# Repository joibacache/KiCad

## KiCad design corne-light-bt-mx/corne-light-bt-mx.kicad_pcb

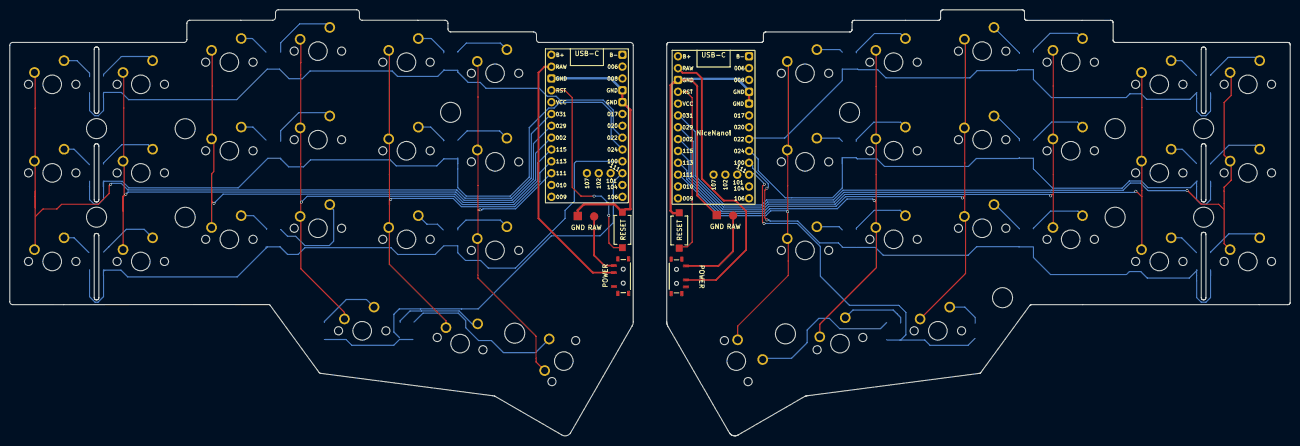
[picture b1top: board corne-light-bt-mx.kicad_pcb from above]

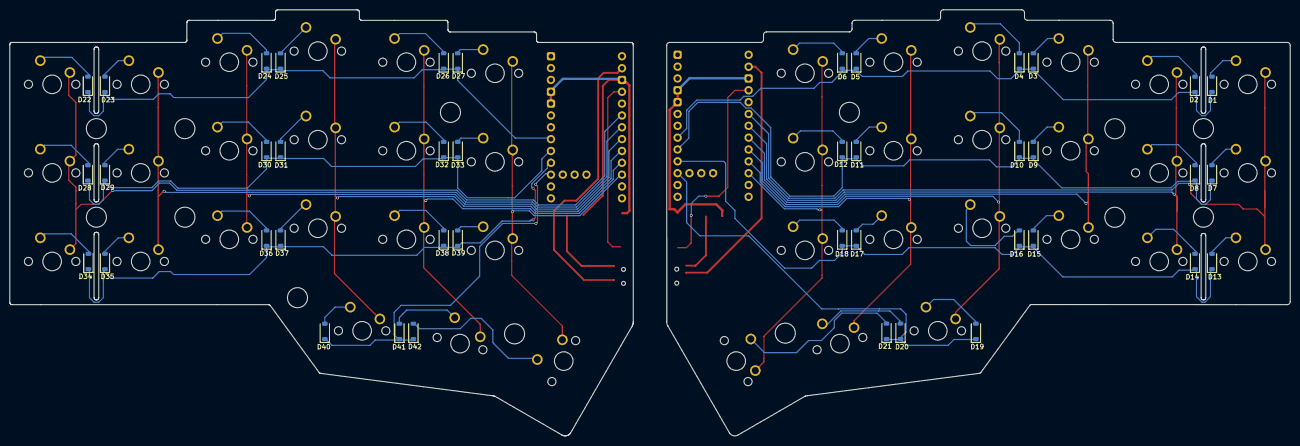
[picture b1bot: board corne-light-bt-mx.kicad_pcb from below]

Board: 2 copper layers, 274.7 x 91.4 mm, 101 parts (44 on the bottom side), 62 nets.

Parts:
D1, D2, D3, D4, D5, D6, D7, D8, D9, D10, D11, D12, D13, D14, D15, D16, D17, D18, D19, D20, D21, D22, D23, D24, D25, D26, D27, D28, D29, D30, D31, D32, D33, D34, D35, D36, D37, D38, D39, D40, D41, D42: D; D_SOD-123
RSW1, RSW2: SW_PUSH; SMD 2Pin Switch
Ref**: Val**; spacer_m2
Ref**#2, Ref**#3, Ref**#4, Ref**#5, Ref**#6, Ref**#7, Ref**#8, Ref**#9, Ref**#10, Ref**#11, Ref**#12, Ref**#13: Val**; spacer_m2
SW1, SW2, SW3, SW4, SW5, SW6, SW7, SW8, SW9, SW10, SW11, SW12, SW13, SW14, SW15, SW16, SW17, SW18, SW19, SW20, SW22, SW23, SW24, SW25, SW26, SW27, SW28, SW29, SW30, SW31, SW32, SW33, SW34, SW35, SW36, SW37, SW38, SW39, SW40, SW41: SW_PUSH; SW_MX_1u
SW21, SW42: SW_PUSH; SW_MX_1.5u
U1, U2: NiceNano!; nice_nano_v2_full

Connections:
unnamed: D1.2, SW1.2
unnamed: D2.2, SW2.2
unnamed: D3.2, SW3.2
unnamed: D4.2, SW4.2
unnamed: D5.2, SW5.2
unnamed: D6.2, SW6.2
unnamed: D7.2, SW7.2
unnamed: D8.2, SW8.2
unnamed: D9.2, SW9.2
unnamed: D10.2, SW10.2
unnamed: D11.2, SW11.2
unnamed: D12.2, SW12.2
unnamed: D13.2, SW13.2
unnamed: D14.2, SW14.2
unnamed: D15.2, SW15.2
unnamed: D16.2, SW16.2
unnamed: D17.2, SW17.2
unnamed: D18.2, SW18.2
unnamed: D19.2, SW19.2
unnamed: D20.2, SW20.2
unnamed: D21.2, SW21.2
unnamed: D22.2, SW22.2
unnamed: D23.2, SW23.2
unnamed: D24.2, SW24.2
unnamed: D25.2, SW25.2
unnamed: D26.2, SW26.2
unnamed: D27.2, SW27.2
unnamed: D28.2, SW28.2
unnamed: D29.2, SW29.2
unnamed: D30.2, SW30.2
unnamed: D31.2, SW31.2
unnamed: D32.2, SW32.2
unnamed: D33.2, SW33.2
unnamed: D34.2, SW34.2
unnamed: D35.2, SW35.2
unnamed: D36.2, SW36.2
unnamed: D37.2, SW37.2
unnamed: D38.2, SW38.2
unnamed: D39.2, SW39.2
unnamed: D40.2, SW40.2
unnamed: D41.2, SW41.2
unnamed: D42.2, SW42.2
col0: SW1.1, SW7.1, SW13.1
col0_r: SW22.1, SW28.1, SW34.1
col1: SW2.1, SW8.1, SW14.1
col1_r: SW23.1, SW29.1, SW35.1
col2: SW3.1, SW9.1, SW15.1
col2_r: SW24.1, SW30.1, SW36.1
col3: SW4.1, SW10.1, SW16.1, SW19.1
col3_r: SW25.1, SW31.1, SW37.1, SW40.1
col4: SW5.1, SW11.1, SW17.1, SW20.1
col4_r: SW26.1, SW32.1, SW38.1, SW41.1
col5: SW6.1, SW12.1, SW18.1, SW21.1
col5_r: SW27.1, SW33.1, SW39.1, SW42.1
row0: D1.1, D2.1, D3.1, D4.1, D5.1, D6.1
row0_r: D22.1, D23.1, D24.1, D25.1, D26.1, D27.1
row1: D7.1, D8.1, D9.1, D10.1, D11.1, D12.1
row1_r: D28.1, D29.1, D30.1, D31.1, D32.1, D33.1
row2: D13.1, D14.1, D15.1, D16.1, D17.1, D18.1
row2_r: D34.1, D35.1, D36.1, D37.1, D38.1, D39.1
row3: D19.1, D20.1, D21.1
row3_r: D40.1, D41.1, D42.1

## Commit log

2024-04-25 First checkin
2024-04-25 Added .gitignore based on KiCad template
2024-04-25 Cleanup
2024-04-27 Corne36 work
